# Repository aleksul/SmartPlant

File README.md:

# SmartPlant

SmartPlant is a simple project that will help you automate watering of your plants.

## Design

Simple and industrial design is easy for 3d printing. Look at this beauty:

## Custom PCB

Custom PCB will polish the look of the final product and make assembling even more simple and fun.

## Ease of modification

Make a fork and rebuild as you want to! 

You can edit any part of this project with open source software such as

- KiCad for schematics and PCB design, 
- FreeCad for 3d modeling, 
- Arduino IDE for code.

## Want to build the same on your own?

Follow the [wiki](https://github.com/Aleksul/SmartPlant/wiki) for Gerber files, bill of materials and more.

## Struggling?

Feel free to open an issue, merge-request or contact me via [Telegram](t.me/aleksul).

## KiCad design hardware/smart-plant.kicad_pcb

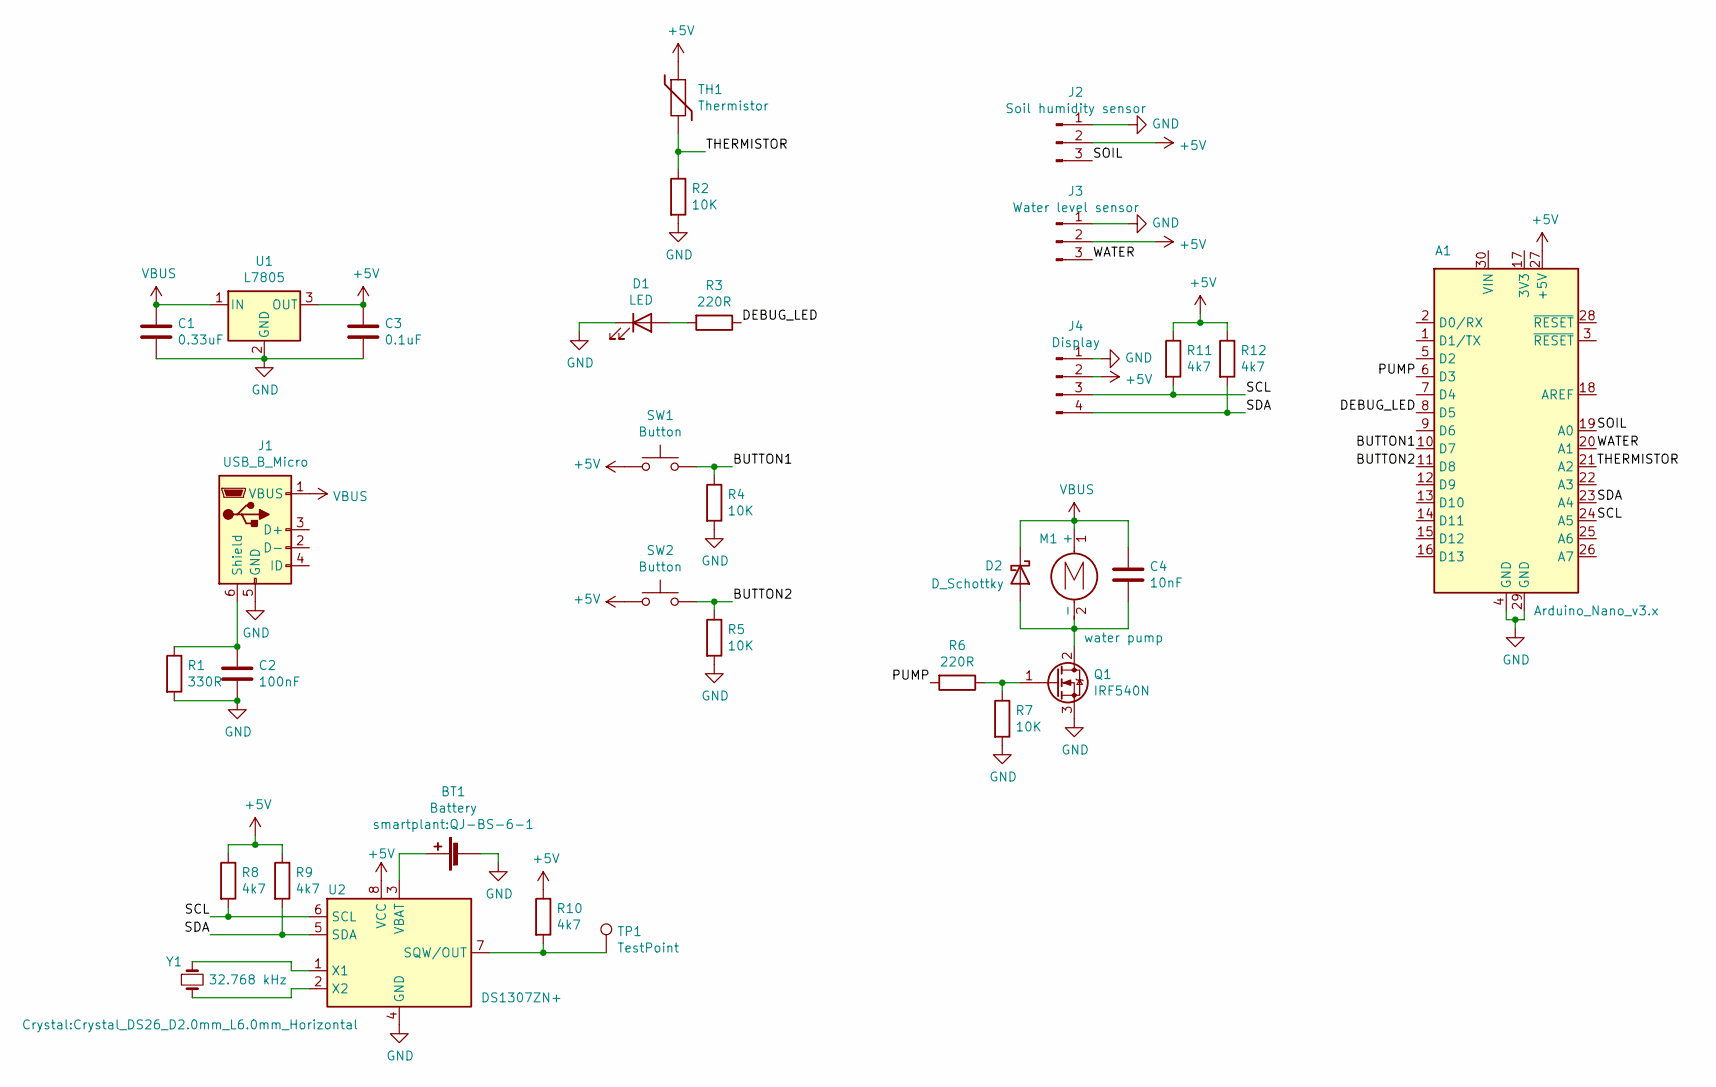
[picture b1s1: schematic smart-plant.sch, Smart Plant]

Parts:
A1: Arduino_Nano_v3.x; Arduino_Nano
BT1: Battery; QJ-BS-6-1
C1: 0.33uF; C_1210_3225Metric_Pad1.33x2.70mm_HandSolder
C2: 100nF; C_1210_3225Metric_Pad1.33x2.70mm_HandSolder
C3: 0.1uF; C_1210_3225Metric_Pad1.33x2.70mm_HandSolder
C4: 10nF; C_1210_3225Metric_Pad1.33x2.70mm_HandSolder
D1: LED; LED_1206_3216Metric
D2: D_Schottky; D_SMB_Handsoldering
J1: USB_B_Micro; USB_Micro-B_Molex-105017-0001
J2: Soil humidity sensor; PinHeader_1x03_P2.54mm_Horizontal
J3: Water level sensor; PinHeader_1x03_P2.54mm_Horizontal
J4: Display; PinHeader_1x04_P2.54mm_Horizontal
M1: water pump; PinHeader_1x02_P2.54mm_Horizontal
Q1: IRF540N; TO-263-2
R1: 330R; R_1210_3225Metric_Pad1.30x2.65mm_HandSolder
R2, R4, R5, R7: 10K; R_1210_3225Metric_Pad1.30x2.65mm_HandSolder
R3, R6: 220R; R_1210_3225Metric_Pad1.30x2.65mm_HandSolder
R8, R9, R10, R11, R12: 4k7; R_1210_3225Metric_Pad1.30x2.65mm_HandSolder
SW1, SW2: Button; SW_PUSH_6mm_H4.3mm
TH1: Thermistor; R_1206_3216Metric_Pad1.30x1.75mm_HandSolder
TP1: TestPoint; TestPoint_Pad_D1.0mm
U1: L7805; TO-263-2
U2: DS1307ZN+; SOIC-8_3.9x4.9mm_P1.27mm
Y1: 32.768 kHz; Crystal_DS26_D2.0mm_L6.0mm_Horizontal

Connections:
+5V: A1.27 (+5V), C3.1, J2.2, J3.2, J4.2, R8.1, R9.1, R10.1, R11.1, R12.1, SW1.1, SW2.1, TH1.1, U1.3 (OUT), U2.8 (VCC)
/BUTTON1: A1.10 (D7), R4.1, SW1.2
/BUTTON2: A1.11 (D8), R5.1, SW2.2
/DEBUG_LED: A1.8 (D5), R3.1
/PUMP: A1.6 (D3), R6.2
/SCL: A1.24 (A5), J4.3, R8.2, R11.2, U2.6 (SCL)
/SDA: A1.23 (A4), J4.4, R9.2, R12.2, U2.5 (SDA)
/SOIL: A1.19 (A0), J2.3
/THERMISTOR: A1.21 (A2), R2.1, TH1.2
/WATER: A1.20 (A1), J3.3
GND: A1.4 (GND), A1.29 (GND), BT1.2 (-), C1.2, C2.2, C3.2, D1.1 (K), J1.5 (GND), J2.1, J3.1, J4.1, Q1.3 (S), R1.2, R2.2, R4.2, R5.2, R7.2, U1.2 (GND), U2.4 (GND)
unnamed: BT1.1 (+), U2.3 (VBAT)
unnamed: C2.1, J1.6 (Shield), R1.1
unnamed: C4.2, D2.2 (A), M1.2 (-), Q1.2 (D)
unnamed: D1.2 (A), R3.2
unnamed: Q1.1 (G), R6.1, R7.1
unnamed: R10.2, TP1.1, U2.7 (SQW/OUT)
unnamed: U2.1 (X1), Y1.1
unnamed: U2.2 (X2), Y1.2
VBUS: C1.1, C4.1, D2.1 (K), J1.1 (VBUS), M1.1 (+), U1.1 (IN)

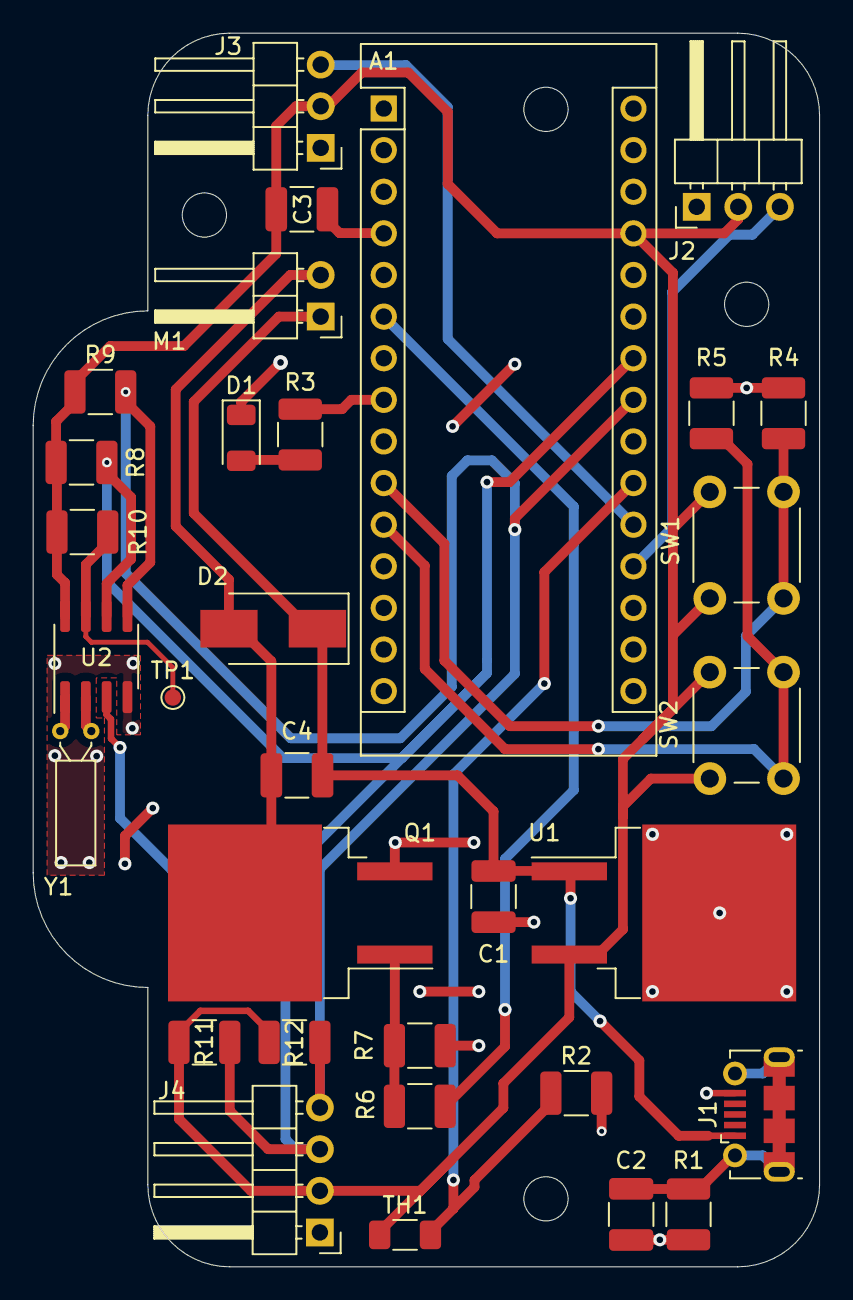
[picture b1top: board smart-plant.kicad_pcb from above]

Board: 2 copper layers, 48.0 x 75.3 mm, 33 parts (1 on the bottom side), 20 nets.

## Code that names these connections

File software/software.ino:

#include <Wire.h>

#include <EEPROM.h>

#include "RTClib.h"
RTC_DS1307 RTC;

#include "Adafruit_GFX.h"
#include "Adafruit_SSD1306.h"

Adafruit_SSD1306 display(128, 32, &Wire, -1);

#define SOIL_SENSOR A0
#define THERMISTOR A2
#define BUTTON1 7
#define BUTTON2 8
#define LED 5
#define PUMP 3

#define PUMP_SEC 15

#define WATER_EVERY_N_SECONDS 259200L

uint16_t maximum_soil_moistry_level = 512;

DateTime future;

String message = "";

void setup()
{
  pinMode(SOIL_SENSOR, INPUT);
  pinMode(THERMISTOR, INPUT);
  pinMode(BUTTON1, INPUT);
  pinMode(BUTTON2, INPUT);
  pinMode(LED, OUTPUT);
  pinMode(PUMP, OUTPUT);
  pinMode(LED_BUILTIN, OUTPUT);

  Wire.begin();

  if (!display.begin(SSD1306_SWITCHCAPVCC, 0x3C)){
    digitalWrite(LED_BUILTIN, HIGH);
    abort(); 
  }
  
  display.clearDisplay();
  display.setTextColor(SSD1306_WHITE);
  display.setCursor(3, 11);
  display.setTextSize(2);
  display.println("SmartPlant");
  display.display();
  delay(3000);
  display.clearDisplay();

  if (!RTC.begin()) {
    digitalWrite(LED_BUILTIN, HIGH);
    abort(); 
  }

  if (! RTC.isrunning()) {
    RTC.adjust(DateTime(F(__DATE__), F(__TIME__)));
  }

  DateTime now = RTC.now();
  future = DateTime(now.unixtime() + WATER_EVERY_N_SECONDS);

  EEPROM.get(2, maximum_soil_moistry_level);

  
}

void loop()
{
  checkButtons();
  DateTime now = RTC.now();
  String old_message = message;
  updateMessage(now, analogRead(SOIL_SENSOR));
  if (old_message != message) {
    updateDisplay();
  }
  if (now.unixtime() >= future.unixtime() && analogRead(SOIL_SENSOR) < maximum_soil_moistry_level) {
    future = DateTime(now.unixtime() + WATER_EVERY_N_SECONDS);
    digitalWrite(PUMP, HIGH);
    delay(PUMP_SEC);
    digitalWrite(PUMP, LOW);
  }
  delay(10);
}

void updateMessage(DateTime now, uint16_t soil) {
  message = "Next watering\n";
  message += "in " + String(future.unixtime() - now.unixtime()) + "s\n";
  if (soil >= maximum_soil_moistry_level) {
    message += "Soil is moist enough";
  }
}

void updateDisplay() {
  display.clearDisplay();
  display.setTextSize(1);
  display.setCursor(0, 0);
  display.println(message);
  display.display();
}

void checkButtons() {
  if (digitalRead(BUTTON2) == HIGH) {
    delay(10);
    if (digitalRead(BUTTON2) == HIGH) {
      maximum_soil_moistry_level = analogRead(SOIL_SENSOR) + 10;
      EEPROM.put(2, maximum_soil_moistry_level);
      digitalWrite(LED, HIGH);
      delay(1000);
      digitalWrite(LED, LOW);
    }
  }
}

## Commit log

2021-05-30 Add schematic and PCB
2021-06-01 Add RTC
2021-07-03 Add pcb and case renders
2021-07-03 Add CONTRIBUTING
2021-07-05 Add jlcpcb gerber
2021-07-07 Add code without display
2021-07-09 Software done
2021-07-09 Fix rtc
2021-07-09 Fix display
2021-07-09 Add 3d model
2021-09-05 Fixed script
